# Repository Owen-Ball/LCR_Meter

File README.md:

# Contents

- [Feature Overview](#feature-overview)
- [Specifications](#specifications)
  - [Frequency Range](#frequency-range)
  - [Autoranging](#autoranging)
  - [Component Ranges](#component-ranges)
  - [Display Parameters](#display-parameters)
  - [Automatic Parameter Selection](#automatic-parameter-selection)
- [Operational Principle](#operational-principle)
  - [Simplified Schematic](#simplified-schematic)
  - [Voltage and Current Phasor Measurement](#voltage-and-current-phasor-measurement)
- [To be placed later](#to-be-placed-later)

# Feature Overview
* Accurate inductance, capacitance, and resistance measurements @ from 100Hz to 75kHz
* Automatic display of relevant component parameters, or ability to manually select 2 displayed parameters
* Support for frequency sweep plots
* Touchscreen and physical button interface
* Open and short probe calibration

# Specifications

## Frequency Range
* 100Hz - 75kHz in increments of 100Hz

## Autoranging
* TIA Gains: 100Ω, 1kΩ, 10kΩ, and 100kΩ
* ADC Input Amps: 1x, 5x, 25x, 100x

## Component Ranges

Parameter | Range
--- | ---
L  | 1uH to 100H
C  | 1pF to 10mF
R  | 1mΩ to 1MΩ

(actual ranges to be confirmed)

## Display Parameters
Parameter | Description
--- | ---
Rs  | Series resistance (ESR/ESL)
Rp  | Parallel resistance
Cs  | Series capacitance
Cp  | Parallel capacitance
Ls  | Series inductance
Lp  | Parallel inductance
Xs  | Series reactance
Q   | Quality factor
D   | Dissipation factor
\|Z\| | Impedance magnitude
∠Z | Impedance angle

## Automatic Parameter Selection

# Operational Principle

This LCR meter uses an auto-balancing bridge design. The general operation of these are as follows:
1. Connect a sinusoidal input voltage to one side of the DUT and the other side to a virtual ground node
2. Read out the voltage across the DUT using a kelvin-connected differential amplifier
3. Convert the current through the DUT into a voltage using a transimpedance amplifier (TIA). Read this out via a differential amplifier
4. Read the voltage and current measurements in via ADCs
5. Calculate the DUT impedance via phasor arithmetic

## Simplified Schematic

At the top of the circuit, an input signal Vin is generated using a buffered and filtered DAC output. This connects to a resistor $R_{range}$ and then the HCUR terminal. The purpose of the $R_{range}$ resistor will be discussed later.

Moving to the bottom of the circuit, the amplifer works to keep the negating amplifer input at ground. This results in a current of 

```math
I_{DUT}(s) = \frac{V_{in}}{Z_{DUT}(s) + R_{range}}
```
flowing through the DUT. This same current will flow through the bottom $R_{range}$ resistor, resulting in an amplifier output of 

```math
I_{meas}(s)=-I_{DUT}(s)\cdot R_{range} = \frac{-V_{in}\cdot R_{range}}{Z_{DUT}(s) + R_{range}}
```

In the middle of the circuit, the voltage across the DUT is read out with kelvin connect lines to remove as much parasitic resistance and inductance from the probe leads. The voltage across the DUT will be 

```math
V_{meas}(s)=I_{DUT}(s)\cdot Z_{DUT}(s)= \frac{V_{in}\cdot Z_{DUT}(s)}{Z_{DUT}(s) + R_{range}}
```

From these two measurements, we can derive $Z_{DUT}(s)$ as

```math
Z_{DUT}(s)=\frac{V_{meas}(s)\cdot R_{range}}{I_{meas}(s)}
```

A couple circuit nuances:
* There are 4 $R_{range}$ resistors, 100Ω, 1kΩ, 10kΩ, and 100kΩ. SNR is highest when $R_{range}$ is close to $|Z_{DUT}(s)|$, so the system automatically switches $R_{range}$ via analog muxes based on measurements. I would recommend reed relays for future derivative projects though.
* For large capacitive DUTs, if the top $R_{range}$ resistor was not present the TIA would be unstable due to the creation of a low frequency pole in the feedback loop. The top resistor introduces a zero at half the frequency of this pole, allowing the loop to be stabilized. While there are other methods to achieve stability with a capacitive load, the introduction of the top $R_{range}$ is particularly useful since it allows stability across a wide range of unknown DUTs and it's accuracy does not actually influence the final calculations.
* While potentially not immediately apparent, it is critical that the current readout is fully differential. At high frequencies the loop gain of the TIA is significantly reduced, resulting in a significant sinusoidal voltage on the virtual ground. So long as the measurements are performed differentially, this effect does not influence the calculations.

Further analysis of this design can be found in this TI reference design: https://www.ti.com/lit/ug/tidueu6b/tidueu6b.pdf

## Voltage and Current Phasor Measurement
https://www.desmos.com/calculator/hkwapyh1lp

# To be placed later:

* Many thanks to the work of WeTec/wschuma. Much of the audio codec design and firmware was based on their work on EEVblog and Github
https://www.eevblog.com/forum/projects/teensylcr-a-teensy-based-diy-lcr-meter/
https://github.com/wschuma/TeensyLCR

* In order to maximize SNR, the system will automatically switch between 4 transimpedance amplifier gains. These gains are 100Ω, 1kΩ, 10kΩ, and 100kΩ. For derivative projects, I would recommend switching to reed relays instead of analog muxes. At high frequenies on the 100kΩ range, the input signal is heavily attenuated

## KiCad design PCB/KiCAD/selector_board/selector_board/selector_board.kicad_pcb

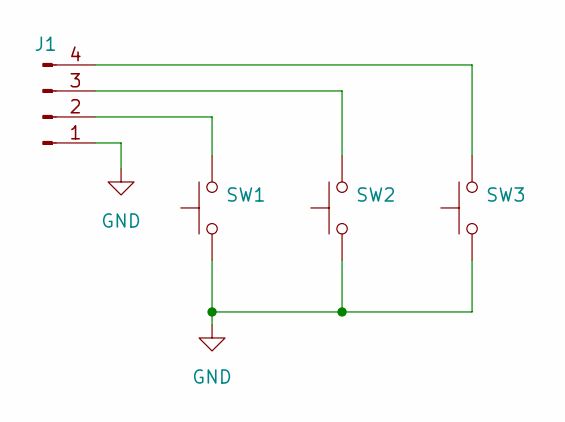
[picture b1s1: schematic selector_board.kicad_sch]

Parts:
J1: Conn_01x04_Pin; PinHeader_1x04_P2.54mm_Vertical
SW1, SW2, SW3: SW_Push; SW_PUSH-12mm

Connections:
GND: J1.1, SW1.1, SW2.1, SW3.1
unnamed: J1.2, SW1.2
unnamed: J1.3, SW2.2
unnamed: J1.4, SW3.2

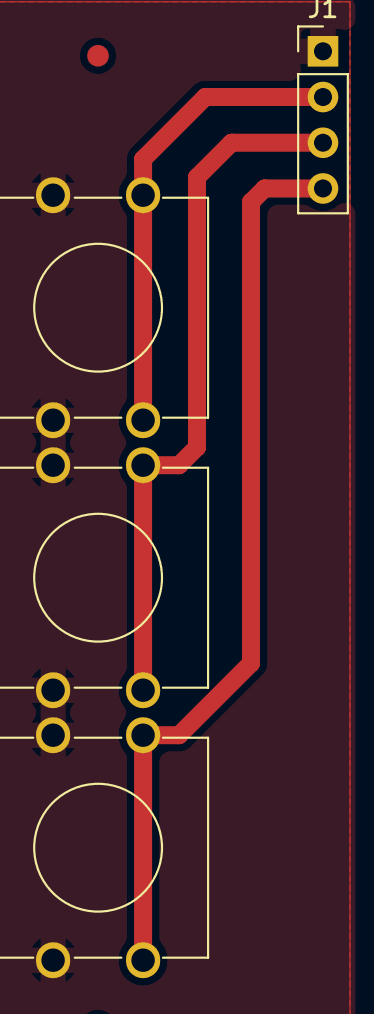
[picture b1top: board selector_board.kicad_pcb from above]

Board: 2 copper layers, 4 parts (0 on the bottom side), 4 nets.

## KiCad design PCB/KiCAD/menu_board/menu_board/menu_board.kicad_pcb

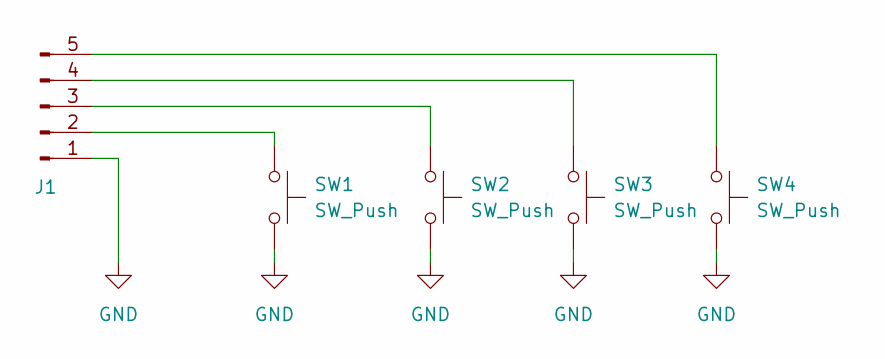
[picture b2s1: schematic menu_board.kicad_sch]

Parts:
J1: Conn_01x05_Pin; PinHeader_1x05_P2.54mm_Vertical
SW1, SW2, SW3, SW4: SW_Push; SW_PUSH_6mm

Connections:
GND: J1.1, SW1.2, SW2.2, SW3.2, SW4.2
unnamed: J1.2, SW1.1
unnamed: J1.3, SW2.1
unnamed: J1.4, SW3.1
unnamed: J1.5, SW4.1

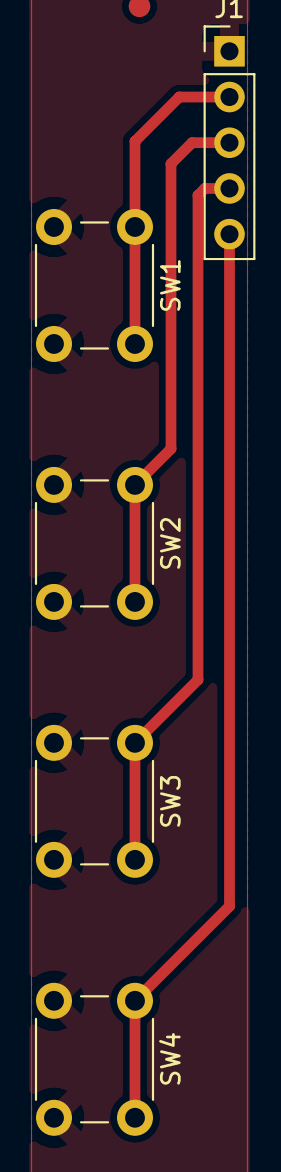
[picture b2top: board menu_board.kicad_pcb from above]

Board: 2 copper layers, 5 parts (0 on the bottom side), 5 nets.

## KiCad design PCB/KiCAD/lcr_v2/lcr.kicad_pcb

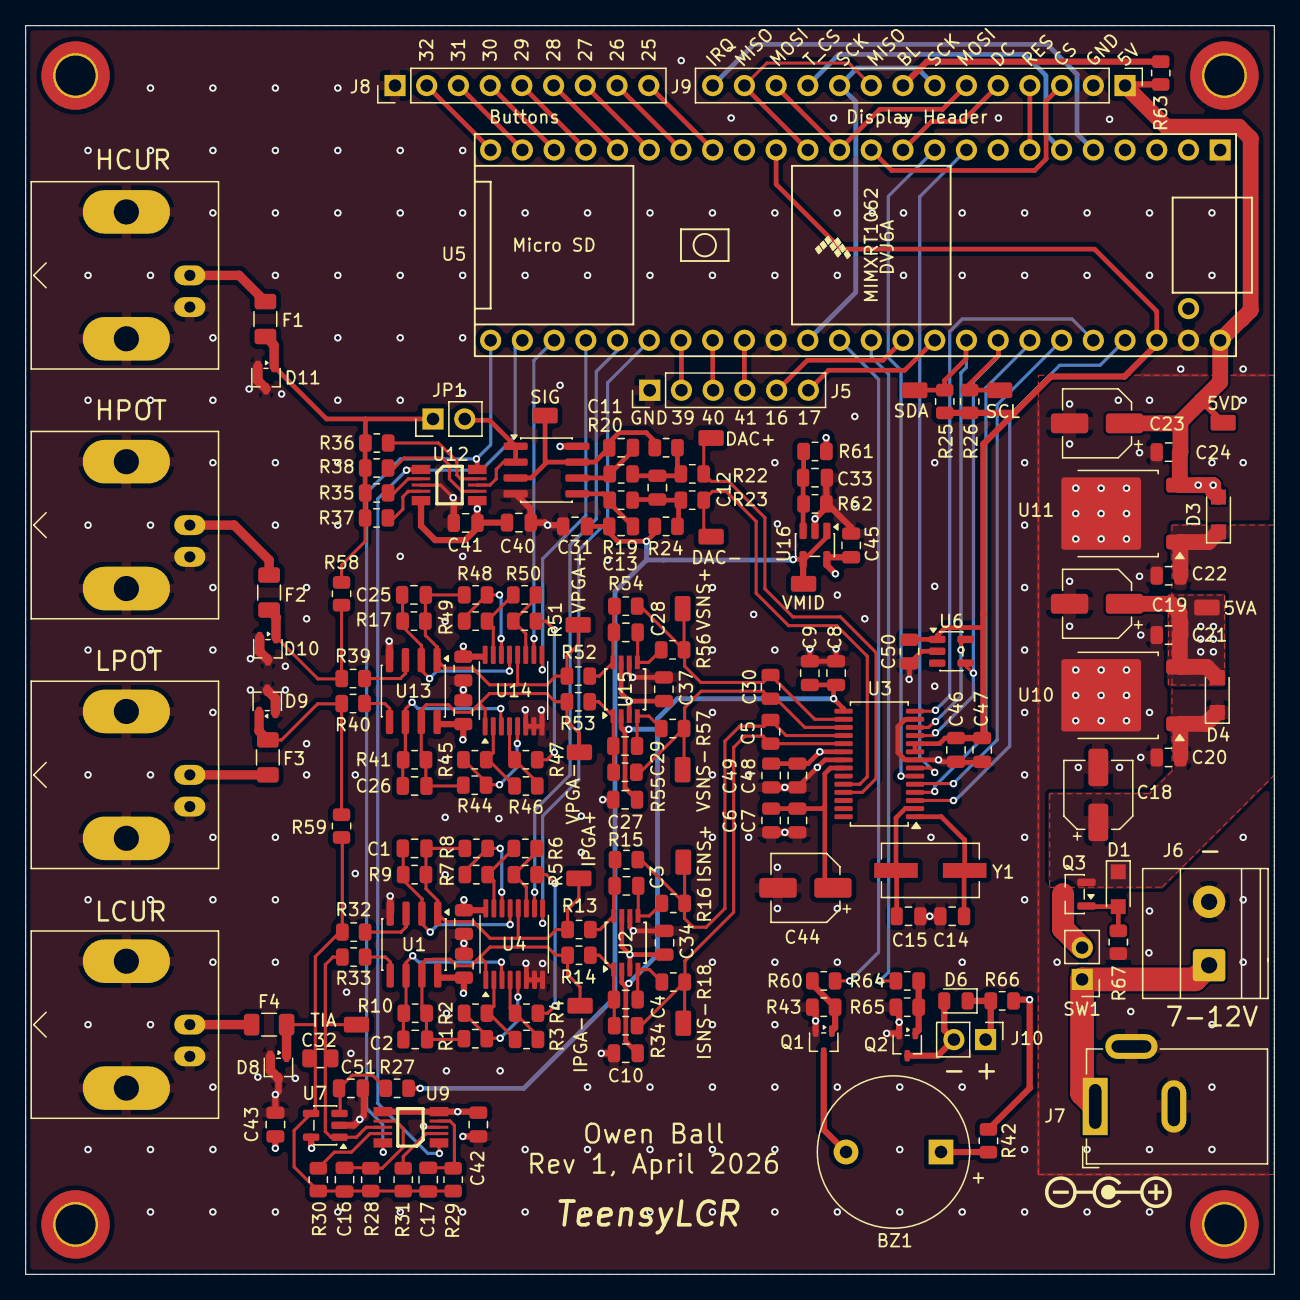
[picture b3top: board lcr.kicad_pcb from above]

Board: 4 copper layers, 100.0 x 100.0 mm, 182 parts (0 on the bottom side), 122 nets.

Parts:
BZ1: Buzzer; Buzzer_12x9.5RM7.6
C1, C2, C16, C17, C25, C26, C32: 1p; C_0805_2012Metric
C3, C4, C28, C29: 470p; C_0805_2012Metric
C5, C30: 2.7n; C_0805_2012Metric
C6, C9, C20, C21, C22, C24, C47, C49: 1u; C_0805_2012Metric
C7, C8, C46, C48: .1u; C_0805_2012Metric
C10, C27, C34, C35, C36, C37, C38, C39, C40, C41, C42, C43, C45, C50, C51: 100n; C_0805_2012Metric
C11, C13, C31: 100p; C_0805_2012Metric
C12: 220p; C_0805_2012Metric
C14, C15: 33p; C_0805_2012Metric
C18, C19, C23, C44: 47u; CP_Elec_5x5.9
C33: 10u; C_0805_2012Metric
D1: 7.5V; Nexperia_CFP3_SOD-123W
D3, D4: D_Schottky; Nexperia_CFP3_SOD-123W
D6: D_Schottky; D_0805_2012Metric
D8, D9, D10, D11: ESD7205; SOT-323_SC-70
F1, F2, F3, F4: 1206L012WR; Fuse_1206_3216Metric
H1, H2, H3, H4: MountingHole_Pad; MountingHole_3.2mm_M3_ISO14580_Pad_TopBottom
J1, J2, J3, J4: Conn_Coaxial; BNC_Amphenol_B6252HB-NPP3G-50_Horizontal
J5: Conn_01x06_Pin; PinHeader_1x06_P2.54mm_Vertical
J6: Screw_Terminal_01x02; TerminalBlock_Phoenix_MKDS-1,5-2-5.08_1x02_P5.08mm_Horizont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
J7: Barrel_Jack_Switch; BarrelJack_GCT_DCJ200-10-A_Horizontal
J8: Conn_01x09_Pin; PinHeader_1x09_P2.54mm_Vertical
J9: Conn_01x14_Pin; PinHeader_1x14_P2.54mm_Vertical
J10: Conn_01x02_Pin; PinHeader_1x02_P2.54mm_Vertical
JP1: Jumper_2_Open; PinHeader_1x02_P2.54mm_Vertical
Q1, Q2: DMG1012UWQ-7; SOT-323_SC-70
Q3: DMP3099L; SOT-23
R1, R8, R21, R24, R44, R48: 8.2k; R_0805_2012Metric
R2, R7, R45, R49: 1.6k; R_0805_2012Metric
R3, R6, R46, R50: 300; R_0805_2012Metric
R4, R5, R31, R35, R47, R51, R60, R63, R64: 100; R_0805_2012Metric
R9, R10, R17, R41: 1M; R_0805_2012Metric
R13, R14, R15, R30, R34, R36, R42, R52, R53, R54, R55: 1k; R_0805_2012Metric
R16, R18, R56, R57: 22; R_0805_2012Metric
R19, R20: 5.1k; R_0805_2012Metric
R22, R23, R29, R37, R43, R58, R59, R61, R62, R65: 10k; R_0805_2012Metric
R25, R26: 3.3k; R_0805_2012Metric
R27: R_US; R_0805_2012Metric
R28, R38, R67: 100k; R_0805_2012Metric
R32, R33, R39, R40, R66: 0; R_0805_2012Metric
SW1: SW_SPST; PinHeader_1x02_P2.54mm_Vertical
TP1: ISNS+; testpoint_0805
TP2: ISNS-; testpoint_0805
TP3: VSNS+; testpoint_0805
TP4: VSNS-; testpoint_0805
TP5: DAC+; testpoint_0805
TP6: DAC-; testpoint_0805
TP7: SIG; testpoint_0805
TP8: IPGA+; testpoint_0805
TP9: IPGA-; testpoint_0805
TP10: VPGA-; testpoint_0805
TP11: VPGA+; testpoint_0805
TP12: 5VA; testpoint_0805
TP13: 5VD; testpoint_0805
TP14: SCL; testpoint_0805
TP15: SDA; testpoint_0805
TP16: TIA; testpoint_0805
TP17: VMID; testpoint_0805
U1, U13: OPA2365AIDR; SOIC-8_3.9x4.9mm_P1.27mm
U2, U15: THS4561IDGKR; TSSOP-8_3x3mm_P0.65mm
U3: CS4272; TSSOP-28_4.4x9.7mm_P0.65mm
U4, U14: DG4052EEQ; TSSOP-16_4.4x5mm_P0.65mm
U5: Teensy4.1_mainpins; Teensy41_mainpins
U6: MCP9800Ax-xOT; SOT-23-5
U7, U16: TLV9161IDBVR; SOT-23-5
U9, U12: DG2034EDQ; MSOP-10_largecorner
U10, U11: MC7805; TO-252-2
U17: TLV9162IDR; SOIC-8_3.9x4.9mm_P1.27mm
Y1: Crystal; Crystal_SMD_ECS_CSM3X-2Pin_7.6x4.1mm

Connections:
+3.3V: C46.2, C47.2, C50.2, R25.1, R26.1, U3.9 (VD), U3.10 (VL), U5.15 (3V3), U5.46 (3V3), U6.1 (V_{DD})
+5VA: C19.1, C21.1, C34.2, C35.2, C36.2, C37.2, C38.2, C39.2, C40.2, C41.2, C42.2, C43.2, C45.2, C48.2, C49.2, D4.2 (A), R61.1, TP12.1 (1_1), U1.8 (V+), U2.3 (V_{S+}), U2.7 (~PD), U3.20 (VA), U4.16 (V+), U7.5 (V+), U9.5 (EN), U9.6 (V+), U10.3 (OUT), U12.5 (EN), U12.6 (V+), U13.8 (V+), U14.16 (V+), U15.3 (V_{S+}), U15.7 (~PD), U16.5 (V+), U17.8 (V+)
+5VD: C23.1, C24.1, D3.2 (A), J9.1, R42.1, R63.1, R66.1, TP13.1 (1_1), U5.48 (VIN), U11.3 (OUT)
+12V: C18.1, C20.1, C22.1, D1.1 (K), D3.1 (K), D4.1 (K), Q3.2 (S), U10.1 (IN), U11.1 (IN)
/BTN1: J8.9, U5.17 (25_A11_RX6_SDA2)
/BTN2: J8.8, U5.18 (26_A12_MOSI1)
/BTN3: J8.7, U5.19 (27_A13_SCK1)
/BTN4: J8.6, U5.20 (28_RX7)
/BTN5: J8.5, U5.21 (29_TX7)
/BTN6: J8.4, U5.22 (30_CRX3)
/BTN7: J8.3, U5.23 (31_CTX3)
/BTN8: J8.2, U5.24 (32_OUT1B)
/BUZZ: R60.1, U5.36 (14_A0_TX3_SPDIF_OUT)
/DISP_CS: J9.3, U5.12 (10_CS_MQSR)
/DISP_DC: J9.5, U5.11 (9_OUT1C)
/DISP_MISO: J9.9, J9.13, U5.14 (12_MISO_MQSL)
/DISP_MOSI: J9.6, J9.12, U5.13 (11_MOSI_CTX1)
/DISP_RESET: J9.4, U5.7 (5_IN2)
/DISP_SCK: J9.7, J9.10, U5.35 (13_SCK_LED)
/DISP_T_CS: J9.11, U5.6 (4_BCLK2)
/DISP_T_IRQ: J9.14, U5.5 (3_LRCLK2)
/FAN_PWM: R64.1, U5.37 (15_A1_RX3_SPDIF_IN)
/GPIO1: J5.6, U5.39 (17_A3_TX4_SDA1)
/GPIO2: J5.5, U5.38 (16_A2_RX4_SCL1)
/GPIO3: J5.4, U5.33 (41_A17)
/GPIO4: J5.3, U5.32 (40_A16)
/GPIO5: J5.2, U5.31 (39_MISO1_OUT1A)
/TIA_FB: C16.1, C17.1, C32.1, D8.1 (K), F4.2, R28.2, R29.2, R30.2, R31.2, R32.2, R59.2, U7.4 (-)
/TIA_OUT: C32.2, R33.2, TP16.1 (1_1), U7.1, U9.8 (COM)
/sig_buf: JP1.2 (B), U12.8 (COM), U17.1, U17.2 (-)
/sig_conn: D11.1 (K), F1.2, JP1.1 (A), R35.2, R36.2, R37.2, R38.2, R58.1
BCLK: U3.5 (SCLK), U5.43 (21_A7_RX5_BCLK1)
CODEC_RST: U3.14 (~RST), U5.44 (22_A8_CTX1)
GND: C6.1, C7.1, C8.1, C9.1, C10.1, C14.2, C15.2, C18.2, C19.2, C20.2, C21.2, C22.2, C23.2, C24.2, C27.1, C31.2, C33.2, C34.1, C35.1, C36.1, C37.1, C38.1, C39.1, C40.1, C41.1, C42.1, C43.1, C44.2, C45.1, C46.1, C47.1, C48.1, C49.1, C50.1, C51.1, D8.2 (K), D8.3 (A), D9.2 (K), D9.3 (A), D10.2 (K), D10.3 (A), D11.2 (K), D11.3 (A), J1.2 (Ext), J2.2 (Ext), J3.2 (Ext), J4.2 (Ext), J5.1, J6.2, J7.2, J7.3, J8.1, J9.2, Q1.2 (S), Q2.2 (S), R43.2, R62.2, R65.2, R67.2, U1.4 (V-), U2.6 (V_{S-}), U3.8 (DGND), U3.13 (AD0/~CS(I2S/~LJ)), U3.21 (AGND), U4.6 (EN), U4.7 (V-), U4.8 (GND), U5.1 (GND), U5.34 (GND), U5.47 (GND), U6.2 (GND), U7.2 (V-), U9.3 (V-), U10.2 (GND), U11.2 (GND), U12.3 (V-), U13.4 (V-), U14.6 (EN), U14.7 (V-), U14.8 (GND), U15.6 (V_{S-}), U16.2 (V-), U17.4 (V-)
ISNS_N: C5.1, R18.1, R34.1, TP2.1 (1_1), U3.19 (AINB-)
ISNS_P: C5.2, R15.2, R16.1, TP1.1 (1_1), U3.18 (AINB+)
LRCLK: U3.4 (LRCK), U5.42 (20_A6_TX5_LRCLK1)
MCLK: U3.3 (MCLK), U5.45 (23_A9_CRX1_MCLK1)
unnamed: BZ1.1 (+), R42.2
unnamed: BZ1.2 (-), Q1.3 (D)
unnamed: C3.2, R16.2, U2.5
unnamed: C4.2, R18.2, U2.4
unnamed: C12.1, R20.1, R21.1, R22.2
unnamed: C12.2, R19.1, R23.2, R24.2
unnamed: C28.2, R56.2, U15.5
unnamed: C29.2, R57.2, U15.4
unnamed: D1.2 (A), Q3.1 (G), R67.1
unnamed: D6.2 (A), J10.2, Q2.3 (D)
unnamed: D6.1 (K), J10.1, R66.2
unnamed: D9.1 (K), F3.2, R40.2, R59.1
unnamed: D10.1 (K), F2.2, R39.2, R58.2
unnamed: F1.1, J1.1 (In)
unnamed: F2.1, J2.1 (In)
unnamed: F3.1, J3.1 (In)
unnamed: F4.1, J4.1 (In)
unnamed: J6.1, J7.1, SW1.1 (A)
unnamed: J9.8, R63.2
unnamed: Q1.1 (G), R43.1, R60.2
unnamed: Q2.1 (G), R64.2, R65.1
unnamed: Q3.3 (D), SW1.2 (B)
unnamed: R4.2, R5.2
unnamed: R47.2, R51.2
unnamed: R32.1, U1.3 (+)
unnamed: C1.1, R9.2, U1.2 (-), U4.13 (X)
unnamed: R33.1, U1.5 (+)
unnamed: C2.1, R10.2, U1.6 (-), U4.3 (Y)
unnamed: C3.1, R13.1, R15.1, U2.8 (+)
unnamed: C4.1, R14.1, R34.2, U2.1 (-)
unnamed: R22.1, TP5.1 (1_1), U3.25 (AOUTA+)
unnamed: R23.1, TP6.1 (1_1), U3.24 (AOUTA-)
unnamed: C6.2, C7.2, C44.1, U3.22 (FILT+)
unnamed: C14.1, U3.1 (XT0), Y1.2
unnamed: C15.1, U3.2 (XTI), Y1.1
unnamed: C1.2, R8.1, R9.1, R13.2, TP8.1 (1_1), U1.1, U4.12 (X0)
unnamed: R7.1, R8.2, U4.14 (X1)
unnamed: R6.1, R7.2, U4.15 (X2)
unnamed: R5.1, R6.2, U4.11 (X3)
unnamed: C2.2, R1.1, R10.1, R14.2, TP9.1 (1_1), U1.7, U4.1 (Y0)
unnamed: R1.2, R2.1, U4.5 (Y1)
unnamed: R2.2, R3.1, U4.2 (Y2)
unnamed: R3.2, R4.1, U4.4 (Y3)
unnamed: C51.2, R27.1, U7.3 (+)
unnamed: R31.1, U9.2 (S1)
unnamed: R30.1, U9.9 (S2)
unnamed: C17.2, R29.1, U9.4 (S3)
unnamed: C16.2, R28.1, U9.7 (S4)
unnamed: R35.1, U12.2 (S1)
unnamed: R36.1, U12.9 (S2)
unnamed: R37.1, U12.4 (S3)
unnamed: R38.1, U12.7 (S4)
unnamed: R39.1, U13.3 (+)
unnamed: C25.1, R17.2, U13.2 (-), U14.13 (X)
unnamed: R40.1, U13.5 (+)
unnamed: C26.1, R41.2, U13.6 (-), U14.3 (Y)
unnamed: C25.2, R17.1, R48.1, R52.2, TP11.1 (1_1), U13.1, U14.12 (X0)
unnamed: R48.2, R49.1, U14.14 (X1)
unnamed: R49.2, R50.1, U14.15 (X2)
unnamed: R50.2, R51.1, U14.11 (X3)
unnamed: C26.2, R41.1, R44.1, R53.2, TP10.1 (1_1), U13.7, U14.1 (Y0)
unnamed: R44.2, R45.1, U14.5 (Y1)
unnamed: R45.2, R46.1, U14.2 (Y2)
unnamed: R46.2, R47.1, U14.4 (Y3)
unnamed: C28.1, R52.1, R54.2, U15.8 (+)
unnamed: C29.1, R53.1, R55.2, U15.1 (-)
unnamed: C33.1, R61.2, R62.1, U16.3 (+)
unnamed: C13.1, R19.2, U17.5 (+)
unnamed: C11.2, R20.2, U17.6 (-)
PGA_I_0: U4.10 (A), U5.29 (37_CS)
PGA_I_1: U4.9 (B), U5.30 (38_CS1_IN1)
PGA_V_0: U5.27 (35_TX8), U14.10 (A)
PGA_V_1: U5.28 (36_CS), U14.9 (B)
RSEL_0: U5.26 (34_RX8), U9.1 (A0), U12.1 (A0)
RSEL_1: U5.25 (33_MCLK2), U9.10 (A1), U12.10 (A1)
SCL: R26.2, TP14.1 (1_1), U3.11 (SCL/CCLK(M0)), U5.41 (19_A5_SCL), U6.4 (SCLK)
SDA: R25.2, TP15.1 (1_1), U3.12 (SDA/CDIN(M1)), U5.40 (18_A4_SDA), U6.5 (SDA)
SDIN: U3.6 (SDOUT(M/~S)), U5.10 (8_TX2_IN1)
SDOUT: U3.7 (SDIN), U5.9 (7_RX2_OUT1A)
SIG_OUT: C11.1, R21.2, TP7.1 (1_1), U17.3 (+), U17.7
VCOM: C8.2, C9.2, C10.2, C27.2, U2.2 (V_{OCM}), U3.15 (VCOM), U15.2 (V_{OCM})
VMID: C13.2, C31.1, R24.1, R27.2, TP17.1 (1_1), U16.1, U16.4 (-)
VSNS_N: C30.1, R55.1, R57.1, TP4.1 (1_1), U3.17 (AINA+)
VSNS_P: C30.2, R54.1, R56.1, TP3.1 (1_1), U3.16 (AINA-)

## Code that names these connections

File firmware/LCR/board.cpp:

#include "board.h"


DMAMEM uint16_t framebuffer[SCREEN_WIDTH * SCREEN_HEIGHT];

Board board;

void Board::init() {
  pinMode(RANGE_SEL_0_PIN, OUTPUT);
  pinMode(RANGE_SEL_1_PIN, OUTPUT);
  pinMode(PGA_V_0_PIN, OUTPUT);
  pinMode(PGA_V_1_PIN, OUTPUT);
  pinMode(PGA_I_0_PIN, OUTPUT);
  pinMode(PGA_I_1_PIN, OUTPUT);

  pinMode(FAN_PIN, OUTPUT);
  pinMode(BUZZER_PIN, OUTPUT);

  enter_button.begin();
  up_button.begin();
  down_button.begin();
  select_button_0.begin();
  select_button_1.begin();
  select_button_2.begin();
  select_button_3.begin();

  setLCRRange(LCR_RANGE_100);
  setPGAGainV(PGA_GAIN_1);
  setPGAGainI(PGA_GAIN_1);

  temp_sensor.begin();
  temp_sensor.writeConfig(MCP9800::ADC_RES_12BITS);

  tft.begin(14000000);
  tft.setRotation(3);
  tft.setFrameBuffer(framebuffer);
  tft.useFrameBuffer(true);
  tft.updateChangedAreasOnly(true);

  ts.begin();
  ts.setRotation(1);

  ts_ignoreuntil = 0;
  ts_state = false;
  
}


void Board::setLCRRange(uint8_t range) {
  board_range = range & 0x03;
  digitalWrite(RANGE_SEL_0_PIN, (board_range >> 0) & 0x01);
  digitalWrite(RANGE_SEL_1_PIN, (board_range >> 1) & 0x01);
}

void Board::setPGAGainV(uint8_t gain) {
  board_gain_v = gain & 0x03;
  digitalWrite(PGA_V_0_PIN, (board_gain_v >> 0) & 0x01);
  digitalWrite(PGA_V_1_PIN, (board_gain_v >> 1) & 0x01);
}

void Board::setPGAGainI(uint8_t gain) {
  board_gain_i = gain & 0x03;
  digitalWrite(PGA_I_0_PIN, (board_gain_i >> 0) & 0x01);
  digitalWrite(PGA_I_1_PIN, (board_gain_i >> 1) & 0x01);
}

bool Board::increaseVGain() {
  if (board_gain_v < PGA_GAIN_NUM-1) {
    setPGAGainV(board_gain_v + 1);
    return true;
  }
  return false;
}

bool Board::decreaseVGain() {
  if (board_gain_v > 0) {
    setPGAGainV(board_gain_v - 1);
    return true;
  }
  return false;
}

bool Board::increaseIGain() {
  if (board_gain_i < PGA_GAIN_NUM-1) {
    setPGAGainI(board_gain_i + 1);
    return true;
  }
  return false;
}

bool Board::decreaseIGain() {
  if (board_gain_i > 0) {
    setPGAGainI(board_gain_i - 1);
    return true;
  }
  return false;
}

bool Board::increaseLCRRange() {
  if (board_range < LCR_RANGE_NUM-1) {
    setLCRRange(board_range + 1);
    return true;
  }
  return false;
}

bool Board::decreaseLCRRange() {
  if (board_range > 0) {
    setLCRRange(board_range - 1);
    return true;
  }
  return false;
}

float Board::getTemperature() {
  return temp_sensor.readTempC16(MCP9800::AMBIENT) / 16.0;
}

uint16_t boundedMap(uint16_t x, uint16_t a1, uint16_t a2, uint16_t b1, uint16_t b2) {
  if (x < a1) return b1;
  if (x > a2) return b2;
  return map(x, a1, a2, b1, b2); 
}

bool Board::tsPressed(long unsigned int debounce_ms) {
  if (tft.asyncUpdateActive()) return false;
  if (millis() < ts_ignoreuntil) return false;

  bool curr_state = ts.touched();

  if (curr_state == ts_state) return false;
  
  ts_ignoreuntil = millis() + debounce_ms;
  ts_state = curr_state;
  
  if (curr_state) {
    TS_Point p = ts.getPoint();
    ts_x = boundedMap(p.x, TS_X_MIN, TS_X_MAX, 0, SCREEN_WIDTH);
    ts_y = boundedMap(p.y, TS_Y_MIN, TS_Y_MAX, 0, SCREEN_HEIGHT);
    return true;
  } else {
    return false;
  }

}

void Board::waitForInput() {
  while (!enter_button.pressed() && !tsPressed()) {
    yield();
  }
}

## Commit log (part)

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2026-03-22 Models and prelim sims
2026-03-22 KiCAD creation
2026-04-11 PCB Files
2026-04-11 Rolling PCB back to autosaved version
2026-04-11 top level pcb routing
2026-04-13 Redoing whole layout
2026-04-14 pcb layout
2026-04-21 Rev 1 PCB files
2026-04-22 Initial firmware commit
2026-04-23 buzzer update and test
2026-04-28 codec test program
2026-04-29 Test code
2026-05-02 Test code updates
2026-05-05 Self cal code
2026-05-10 Self calibration
    Self calibration largely finished and tested.
    Save and load of calibration implementation finalized.
    Selection/linear interpolation of calibration data
2026-05-13 Calibration + impedance functions
2026-05-15 Float printing
    Added class for formatted float printing with metric prefixes and fixed # of digits
2026-05-22 Menu test code
2026-05-23 menu code development
2026-05-24 menu code moved into main project
2026-05-24 Menu integration
2026-05-26 Menu interaction with system
    Also fixed a nasty little bug with function pointers inside the Complex class in the calibration struct. Calling print on the calibration data values without first copying the calibration data to a d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
2026-05-28 Refactor of startup code
2026-05-29 Moving code from desktop to laptop
2026-06-03 LCR parameter printing code
2026-06-05 display text
2026-06-06 Auto LCR param selection
    You know I feel like I started this code base out so well... Nice segmentation of the code via handy classes, structs, etc. Definitely devolving a bit with how the FSM communicates with various other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
2026-06-07 Log printing code
2026-06-09 Cal display code
    Some more sloppy code but it works.
    More than pretty enough for a procedure that I hope is not used much. The probe cal is the nicest, which reflects that being the most commonly used
2026-06-13 Cal saving display
2026-06-13 Min number resolution + font update
2026-06-14 Z overflow and beginning freq selector
2026-06-16 freq selector code
2026-06-18 Frequency selector
    Added support for holding down button and showing selected digit. Can now exit selector mode and menu bar updates with appropriate frequency
2026-06-23 Amp selector
2026-06-24 Mode selector start
2026-06-24 custom font characters
2026-06-25 Display for param select mode
2026-06-27 Multiple probe type cals
2026-06-27 Firmware reorg + probe toggle
2026-06-28 moving average filter
2026-06-28 polar plotter
